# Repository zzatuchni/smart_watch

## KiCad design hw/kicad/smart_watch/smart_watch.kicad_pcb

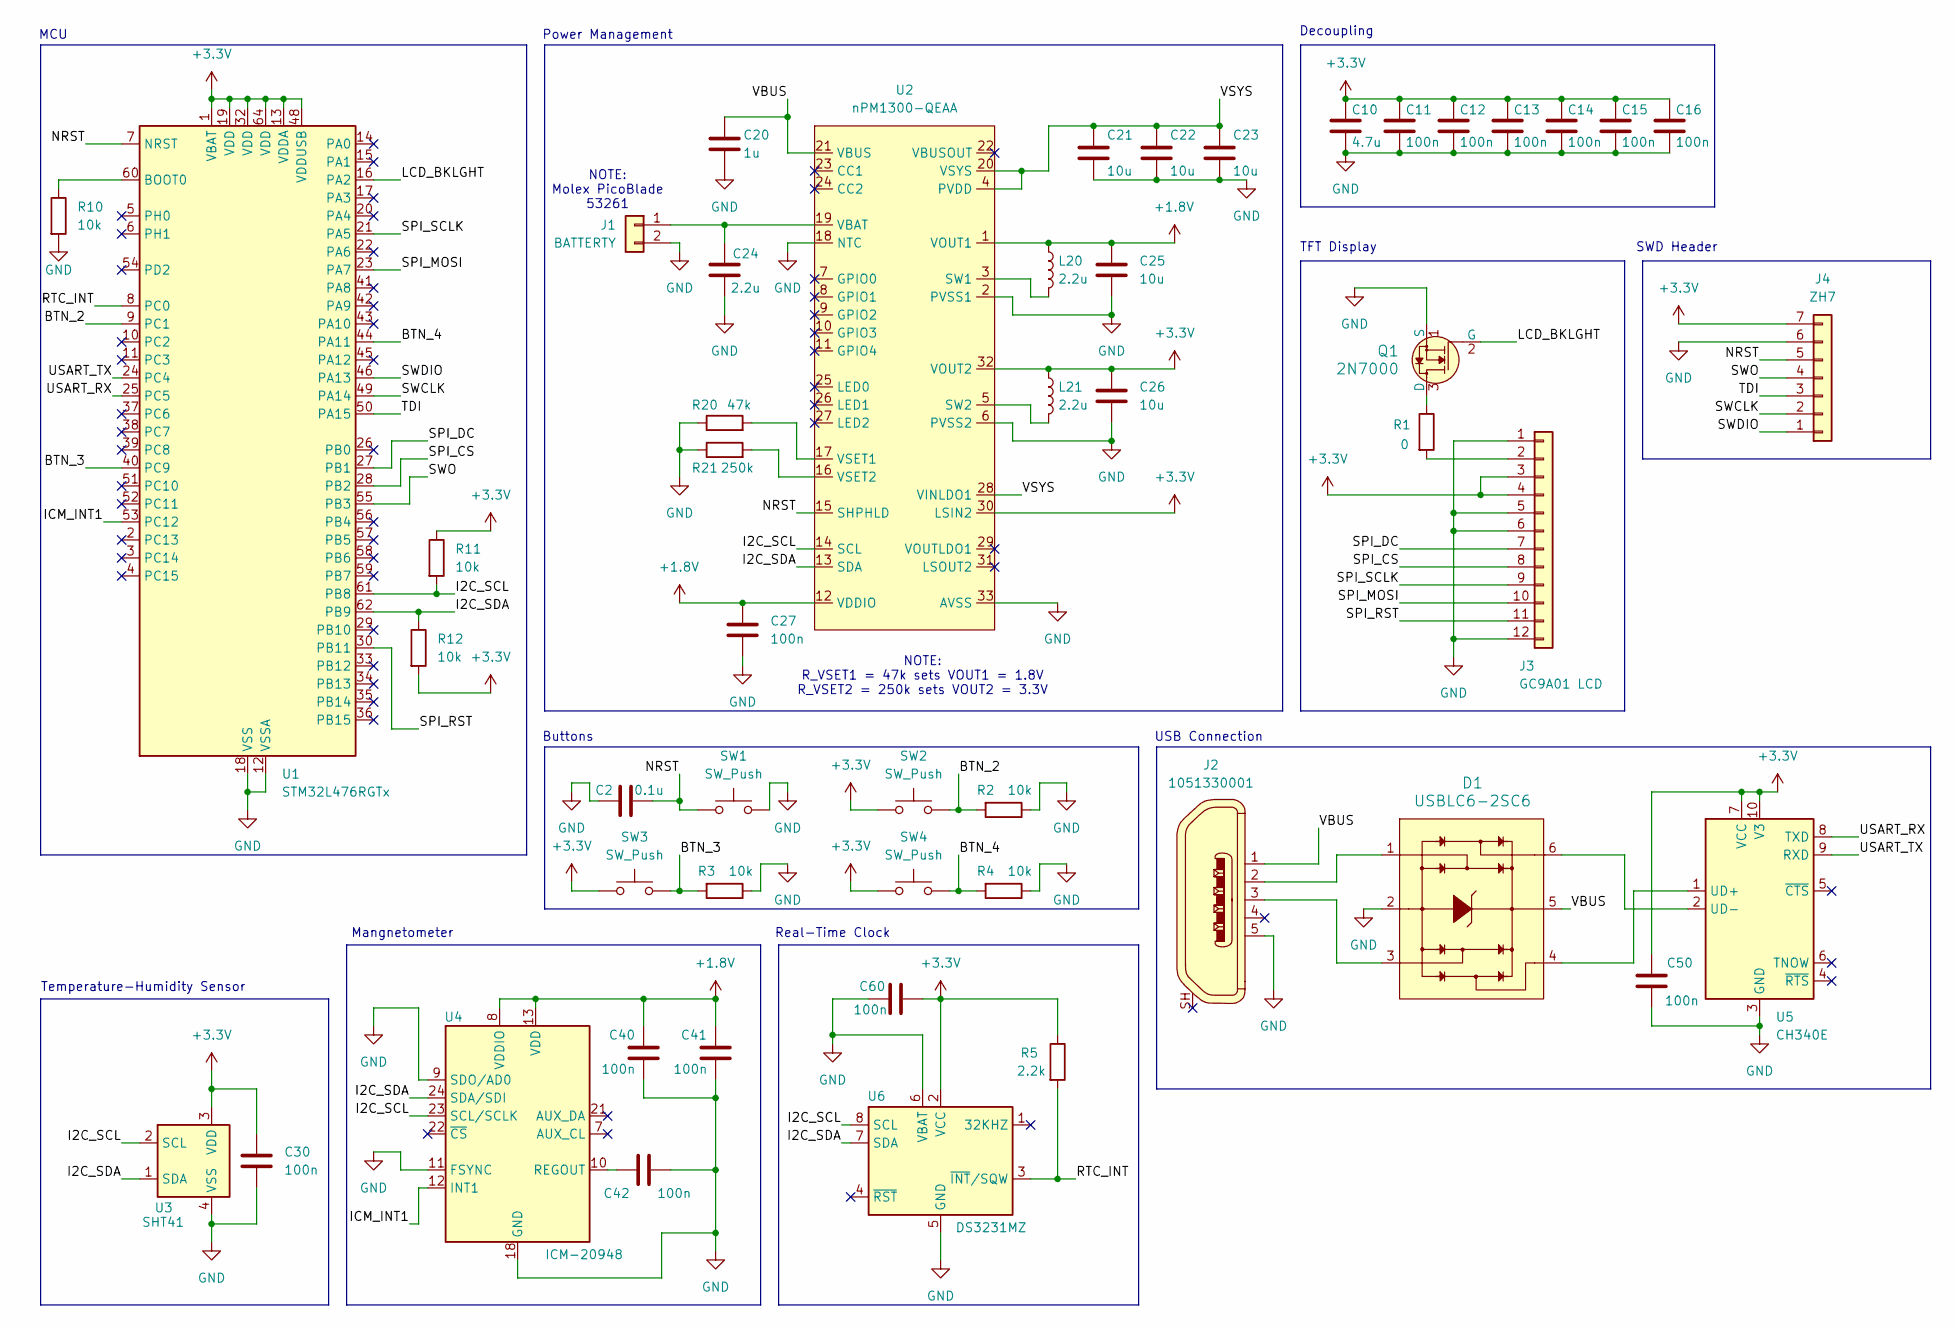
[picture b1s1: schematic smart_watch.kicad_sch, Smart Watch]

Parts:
C2: 0.1u; C_0603_1608Metric
C10: 4.7u; C_0603_1608Metric
C11, C12, C13, C14, C15, C16, C27, C30, C40, C41, C42, C50, C60: 100n; C_0603_1608Metric
C20: 1u; C_0603_1608Metric
C21, C22, C23, C25, C26: 10u; C_0603_1608Metric
C24: 2.2u; C_0603_1608Metric
D1: USBLC6-2SC6; SOT23-6L; MPN USBLC6-2SC6; Digi-Key_PN 497-5235-1-ND
J1: BATTERTY; Molex_PicoBlade_53261-0271_1x02-1MP_P1.25mm_Horizontal
J2: 1051330001; USB_Micro_B_Female_Vert_1051330001; MPN 1051330001; Digi-Key_PN WM9734CT-ND
J3: GC9A01 LCD; GC9A01_FPC_pads_P0.7mm
J4: ZH7; JST_ZH_S7B-ZR-SM4A-TF_1x07-1MP_P1.50mm_Horizontal
L20, L21: 2.2u; L_0603_1608Metric
Q1: 2N7000; SOT-23; MPN 2N7000; Digi-Key_PN 2N7000FS-ND
R1: 0; R_0603_1608Metric
R2, R3, R4, R10, R11, R12: 10k; R_0603_1608Metric
R5: 2.2k; R_0603_1608Metric
R20: 47k; R_0603_1608Metric
R21: 250k; R_0603_1608Metric
SW1, SW2, SW3, SW4: SW_Push; TL6340
U1: STM32L476RGTx; LQFP-64_10x10mm_P0.5mm
U2: nPM1300-QEAA; nPM1300
U3: SHT41; Sensirion_DFN-4_1.5x1.5mm_P0.8mm_SHT4x_NoCentralPad
U4: ICM-20948; InvenSense_QFN-24_3x3mm_P0.4mm
U5: CH340E; MSOP-10_3x3mm_P0.5mm
U6: DS3231MZ; SOIC-8_3.9x4.9mm_P1.27mm

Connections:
+1.8V: C25.1, C27.1, C40.2, C41.2, L20.1, U2.1 (VOUT1), U2.12 (VDDIO), U4.8 (VDDIO), U4.13 (VDD)
/BTN_2: R2.2, SW2.2, U1.9 (PC1)
/BTN_3: R3.2, SW3.2, U1.40 (PC9)
/BTN_4: R4.2, SW4.2, U1.44 (PA11)
/I2C_SCL: R11.2, U1.61 (PB8), U2.14 (SCL), U3.2 (SCL), U4.23 (SCL/SCLK), U6.8 (SCL)
/I2C_SDA: R12.1, U1.62 (PB9), U2.13 (SDA), U3.1 (SDA), U4.24 (SDA/SDI), U6.7 (SDA)
/ICM_INT1: U1.53 (PC12), U4.12 (INT1)
/LCD_BKLGHT: Q1.2 (G), U1.16 (PA2)
/NRST: C2.2, J4.5, SW1.1, U1.7 (NRST), U2.15 (SHPHLD)
/RTC_INT: R5.2, U1.8 (PC0), U6.3 (~INT/SQW)
/SPI_CS: J3.8, U1.28 (PB2)
/SPI_DC: J3.7, U1.27 (PB1)
/SPI_MOSI: J3.10, U1.23 (PA7)
/SPI_RST: J3.11, U1.30 (PB11)
/SPI_SCLK: J3.9, U1.21 (PA5)
/SWCLK: J4.2, U1.49 (PA14)
/SWDIO: J4.1, U1.46 (PA13)
/SWO: J4.4, U1.55 (PB3)
/TDI: J4.3, U1.50 (PA15)
/USART_RX: U1.25 (PC5), U5.8 (TXD)
/USART_TX: U1.24 (PC4), U5.9 (RXD)
/VBUS: C20.1, D1.5, J2.1, U2.21 (VBUS)
/VSYS: C21.2, C22.2, C23.2, U2.4 (PVDD), U2.20 (VSYS), U2.28 (VINLDO1)
unnamed: D1.1, J2.2
unnamed: D1.3, J2.3
unnamed: C24.1, J1.1, U2.19 (VBAT)
unnamed: J3.2, R1.2
unnamed: Q1.3 (D), R1.1
unnamed: R10.1, U1.60 (BOOT0)
unnamed: L20.2, U2.3 (SW1)
unnamed: L21.2, U2.5 (SW2)
unnamed: R20.2, U2.17 (VSET1)
unnamed: R21.2, U2.16 (VSET2)
unnamed: C42.2, U4.10 (REGOUT)
unnamed: D1.4, U5.1 (UD+)
unnamed: D1.6, U5.2 (UD-)

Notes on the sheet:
Mangnetometer
SWD Header
NOTE: Molex PicoBlade 53261
Temperature-Humidity Sensor
USB Connection
TFT Display
Power Management
Real-Time Clock
Buttons
NOTE: R_VSET1 = 47k sets VOUT1 = 1.8V R_VSET2 = 250k sets VOUT2 = 3.3V
MCU
Decoupling

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
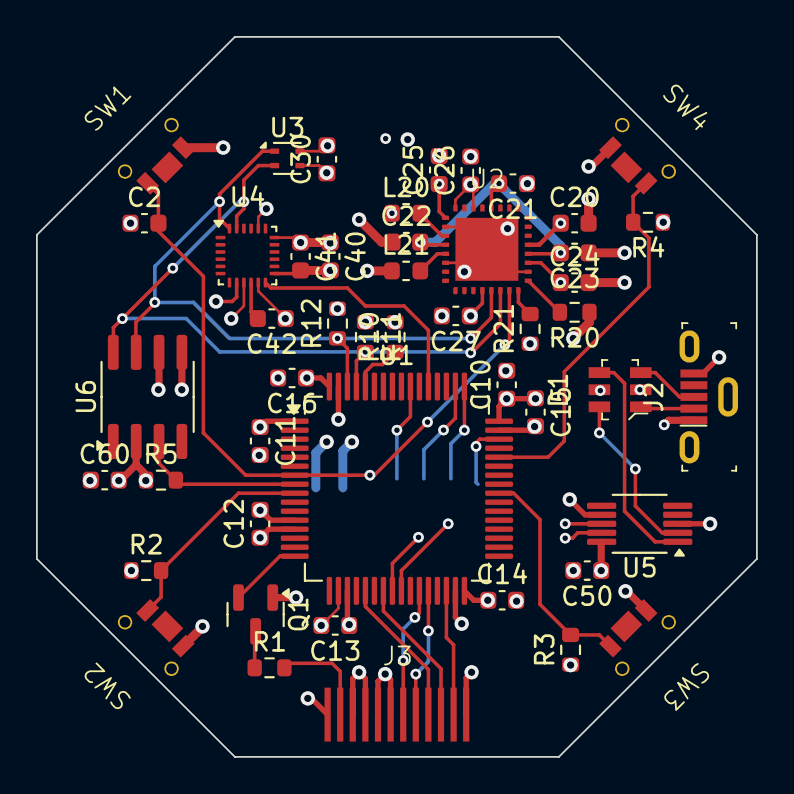
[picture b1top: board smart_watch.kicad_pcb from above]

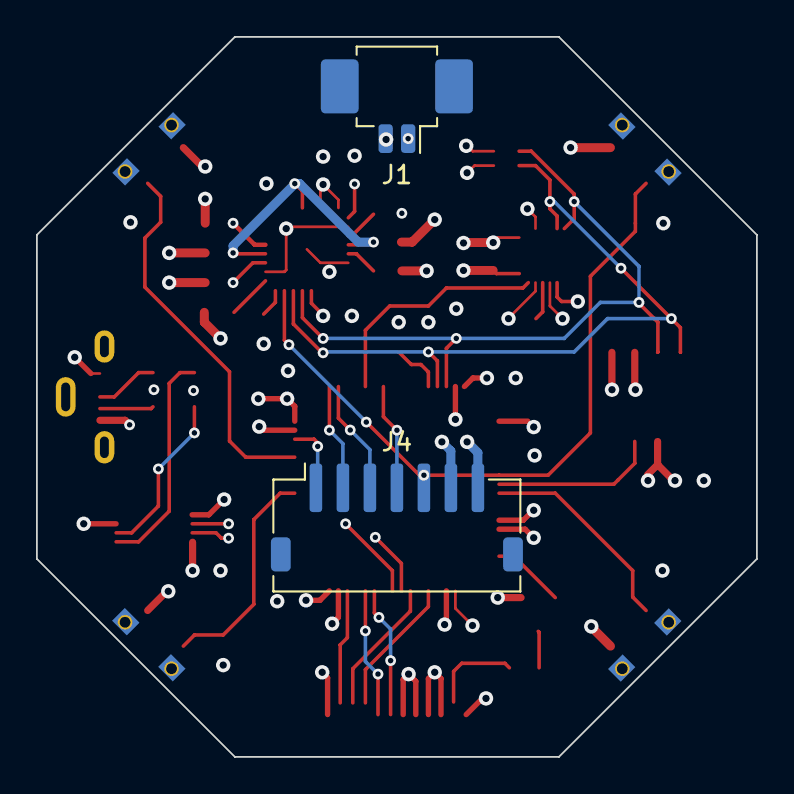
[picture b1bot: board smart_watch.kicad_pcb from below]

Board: 4 copper layers, 40.0 x 40.0 mm, 50 parts (2 on the bottom side), 38 nets.

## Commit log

2024-11-25 smart watch high level diagram
2024-12-05 begin software
2024-12-06 uart communication
2024-12-08 lcd startup
2024-12-09 starting with rtc
2024-12-11 rtc polling accurate
2024-12-13 getting patterns on LCD
2024-12-14 displaying numbers on the lcd
2024-12-17 better debugging/helper functions
2024-12-18 preparing to write os
2025-01-08 starting i2c
2025-01-09 more i2c
2025-01-11 Start schematic
2025-01-12 setting the rtc time
2025-01-14 block diagram
2025-01-15 work on kicad schematic
2025-01-19 i2c works
2025-01-19 getting magnetic data
2025-01-23 get compass degrees attempt 1
2025-01-29 schematic
2025-02-02 schematic done?
2025-02-03 pmic footprint
2025-02-06 more part selection pt 1
2025-02-07 start pcb
2025-02-09 added rtc chip to board
2025-02-11 pcb design part 1
2025-02-12 pcb design part 2
2025-02-21 layout attempt 2
2025-02-23 layout attempt 2 part 2
2025-02-23 layout attempt 2 part 3
2025-03-20 back at the pcb design
2025-04-23 Starting this again
2025-05-02 pcb design again pt 1
2025-05-04 pcb design again pt 2
2025-05-08 pcb design again pt 3
2025-05-13 pcb design again pt 4
2025-07-03 improving the font
2025-07-22 placement of numbers on screen
